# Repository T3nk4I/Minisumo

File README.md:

# Minisumo
Code and Files for all the minisumo and sumo related projects I make, this repository includes codes, schematics, drawings, 3D files and more to make your own minisumo robot.\
**Important: These are mostly personal projects, there might be some errors that will be fixed and updated, but I'm not responsable for any damage or malfunction that is caused by using the codes, files, etc. provided in this repository. If you find any errors in my code, PCBs, or any improvements in the 3D designs feel free to comment so I can correct the design, you can also make a pull request**

*The projects marked in italic are projects that are still on progress*

# Why open source?
When I started there was little to no info on how to make this kind of competition robots, so I want to make newcomers an easy and accesible database.
Also anyone interested in making changes or upgrades can do them depending on their design choice and taste.

# Folders

## PCB's
- Main boards:
  - Tei: PCB for minisumo using arduino nano and TB6612FNG
  - Tenn: PCB for minisumo using arduino nano and DRV8871 drivers
  - Inn BEC: Battery Eliminator Circuit, (AKA buck converter) using XL1509 IC, supports up to 36V and has 5V output, also has a L7805 footprint in the back so it can be adaptable.
  - Ma: PCB using SMD atmega 328P and MSKSEMI RZ7899-MS drivers
  - *Jyo: PCB for microsumo using Seeeduino Xiao and DRV7781 drivers*
- Sensors:
    - QTMicro: Microsized line sensor suitable for minisumo and microsumo robots
## Code
- Basic: basic minisumo code without line sensors and 2 opponent sensors
- *SumoESP: minisumo code for the Arduino Nano ESP model*
- Tamashi-I7ach1: main code used for minisumo robot I7ach1 which uses a ESP32-C3 as the main board
- Tamashi-T4nook1: main code used for minisumo robot T4nook1 which uses a atmega328p as the main controller
- Tamashi-K1tsun3: main code used for minisumo robot K1tsun3 which uses a atmega328p as the main controller
## 3D Data
- Flag System: DAMASHI-FLAG-SYSTEM, used for minisumo robots, compatible with the "OH", "JIN" and "MA-JIN" motor brackets.
- Motor brackets:
  - OH: motor bracket compatible for the minisumo robot chasis in this repository, it can hold 050 style motors
  - JIN: motor bracket compatible for the minisumo robot chasis in this repository, it can hold maxon motors
  - MA-JIN: same as JIN motor bracket, but it can host a qtr-micro line sensor in the back.
- Robots
  - Gyu-Ma-Oh: The base and the chasis files for Gyu-Ma-Oh, 4 oponent sensors and 1 line sensor.
  - T4nook1: The base and the chasis files for T4nook1, 4 oponent sensors and 2 line sensors.
  - K1tsun3: The base and the chasis files for K1tsun3, 5 oponent sensors and 2 line sensors.

# Software that I use
For the most part I try to make all the files as modifiable as possible, but in some cases like the PCB's it's not that possible, so here's a list of software that you can use for the different extensions and file types in this repo.

- 3D data: I mainly use FUSION360 and **[FreeCAD](https://www.freecad.org/)** but I upload the files in .IGES and .STL so you can use any 3D CAD software and slicer software out there to modify and/or print the parts.
- PCB's: I upload the gerbers in zip format for easy fabrication, I also upload a separate gerber file and BOM for **[JLPCB](https://jlcpcb.com/)**  fabrication. As for modifying the files I use **[Kicad](https://www.kicad.org/)** which is a free and open source EDA.
- Code: I use Visual Studio Code with the **[PlatformIO](https://platformio.org/)** extension, but the framework I work on is the arduino framework, so you can use the **[ArduinoIDE](https://www.arduino.cc/en/software)** if you want.

---
You can also visit my ORG. page, **[DENJU DIVISION](https://github.com/DENJU-DIVISION)** where we upload the different files individually, we upload mainly the boards that we have already tested and functioned without problems.

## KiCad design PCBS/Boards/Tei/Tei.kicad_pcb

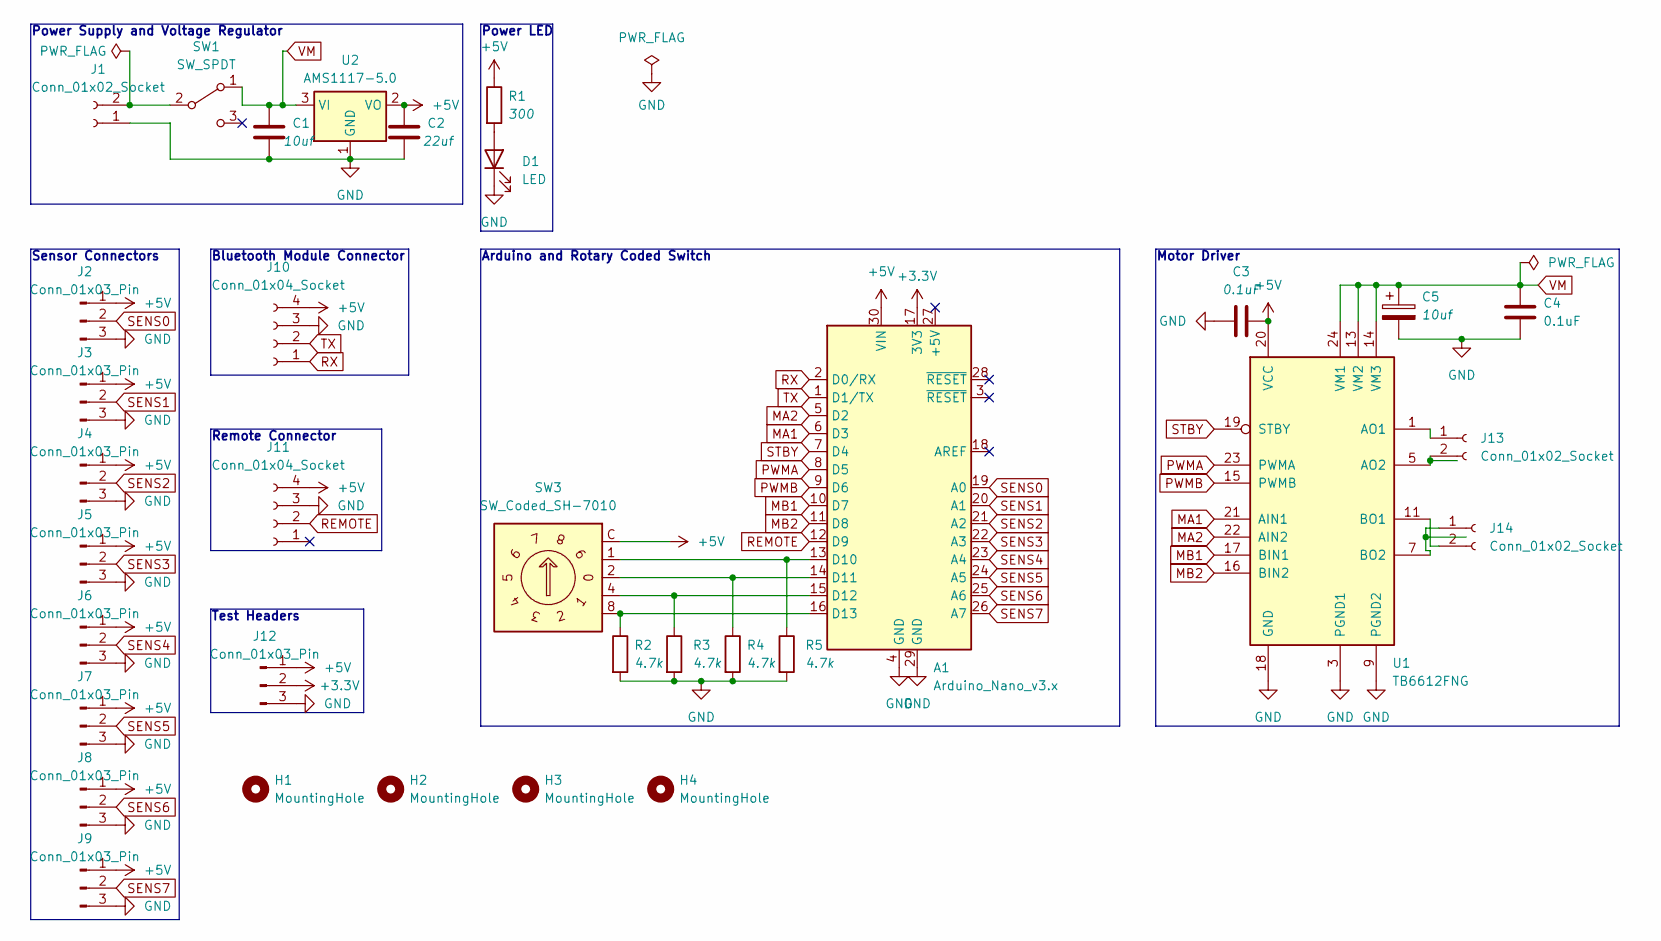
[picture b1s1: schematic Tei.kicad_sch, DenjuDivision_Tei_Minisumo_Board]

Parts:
A1: Arduino_Nano_v3.x; Arduino_Nano
C1: 10uf; C_0805_2012Metric_Pad1.18x1.45mm_HandSolder
C2: 22uf; C_0805_2012Metric_Pad1.18x1.45mm_HandSolder
C3, C4: 0.1uF; C_0805_2012Metric_Pad1.18x1.45mm_HandSolder
C5: 10uf; CP_EIA-3216-18_Kemet-A
D1: LED; LED_0805_2012Metric_Pad1.15x1.40mm_HandSolder
H1, H2, H3, H4: MountingHole; MountingHole_2.2mm_M2
J1: Conn_01x02_Socket; AMASS_XT30U-F_1x02_P5.0mm_Vertical
J2, J3, J4, J5, J6, J7, J8, J9, J12: Conn_01x03_Pin; PinHeader_1x03_P2.54mm_Vertical
J10, J11: Conn_01x04_Socket; PinSocket_1x04_P2.54mm_Vertical
J13, J14: Conn_01x02_Socket; JST_XH_B2B-XH-A_1x02_P2.50mm_Vertical
R1: 300; R_0805_2012Metric_Pad1.20x1.40mm_HandSolder
R2, R3, R4, R5: 4.7k; R_0805_2012Metric_Pad1.20x1.40mm_HandSolder
SW1: SW_SPDT; SW_SPDT_PCM12
SW3: SW_Coded_SH-7010; Nidec_Copal_SH-7010A
U1: TB6612FNG; SSOP-24_5.3x8.2mm_P0.65mm
U2: AMS1117-5.0; SOT-223-3_TabPin2

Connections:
+3.3V: A1.17 (3V3), J12.2
+5V: A1.30 (VIN), C2.1, C3.2, J2.1, J3.1, J4.1, J5.1, J6.1, J7.1, J8.1, J9.1, J10.4, J11.4, J12.1, R1.1, SW3.C, U1.20 (VCC), U2.2 (VO); also elsewhere on the board
GND: A1.4 (GND), A1.29 (GND), C1.2, C2.2, C3.1, C4.1, C5.2, D1.1 (K), J1.1, J2.3, J3.3, J4.3, J5.3, J6.3, J7.3, J8.3, J9.3, J10.3, J11.3, J12.3, R2.2, R3.2, R4.2, R5.2, U1.3 (PGND1), U1.4 (PGND1), U1.9 (PGND2), U1.10 (PGND2), U1.18 (GND), U2.1 (GND); also elsewhere on the board
MA1: A1.6 (D3), U1.21 (AIN1)
MA2: A1.5 (D2), U1.22 (AIN2)
MB1: A1.10 (D7), U1.17 (BIN1)
MB2: A1.11 (D8), U1.16 (BIN2)
unnamed 7: A1.13 (D10), R5.1, SW3.1; also elsewhere on the board
unnamed 8: A1.14 (D11), R4.1, SW3.2; also elsewhere on the board
unnamed 9: A1.15 (D12), R3.1, SW3.4; also elsewhere on the board
unnamed 10: A1.16 (D13), R2.1, SW3.8; also elsewhere on the board
unnamed: D1.2 (A), R1.2
unnamed: J1.2, SW1.2 (B)
unnamed: J13.1, U1.1 (AO1), U1.2 (AO1)
unnamed: J13.2, U1.5 (AO2), U1.6 (AO2)
unnamed: J14.1, U1.7 (BO2), U1.8 (BO2)
unnamed: J14.2, U1.11 (BO1), U1.12 (BO1)
PWMA: A1.8 (D5), U1.23 (PWMA)
PWMB: A1.9 (D6), U1.15 (PWMB)
REMOTE: A1.12 (D9), J11.2; also elsewhere on the board
RX: A1.2 (D0/RX), J10.1; also elsewhere on the board
SENS0: A1.19 (A0), J2.2
SENS1: A1.20 (A1), J3.2
SENS2: A1.21 (A2), J4.2
SENS3: A1.22 (A3), J5.2
SENS4: A1.23 (A4), J6.2
SENS5: A1.24 (A5), J7.2
SENS6: A1.25 (A6), J8.2
SENS7: A1.26 (A7), J9.2
STBY: A1.7 (D4), U1.19 (STBY)
TX: A1.1 (D1/TX), J10.2; also elsewhere on the board
VM: C1.1, C4.2, C5.1, SW1.1 (A), U1.13 (VM2), U1.14 (VM3), U1.24 (VM1), U2.3 (VI)

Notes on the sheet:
Remote Connector
Arduino and Rotary Coded Switch
Sensor Connectors
Test Headers
Bluetooth Module Connector
Power Supply and Voltage Regulator
Power LED
Motor Driver

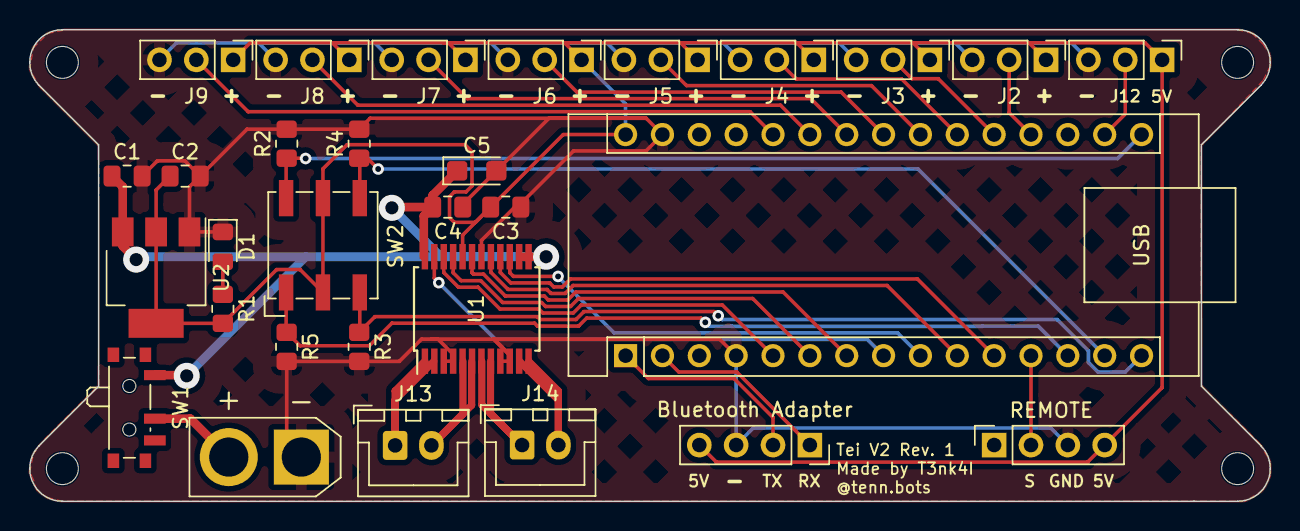
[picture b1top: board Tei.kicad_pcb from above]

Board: 2 copper layers, 85.5 x 32.5 mm, 34 parts (0 on the bottom side), 32 nets.

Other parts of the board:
Bluetooth Adapter: Conn_01x04_Socket; PinSocket_1x04_P2.54mm_Vertical
REMOTE: Conn_01x04_Socket; PinSocket_1x04_P2.54mm_Vertical
SW2: SW_Coded_SH-7010; Nidec_Copal_SH-7010A

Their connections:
+5V: Bluetooth Adapter.4, REMOTE.4, SW2.C; also elsewhere on the board
GND: Bluetooth Adapter.3, REMOTE.3; also elsewhere on the board
unnamed 7: SW2.1; also elsewhere on the board
unnamed 8: SW2.2; also elsewhere on the board
unnamed 9: SW2.4; also elsewhere on the board
unnamed 10: SW2.8; also elsewhere on the board
REMOTE: REMOTE.2; also elsewhere on the board
RX: Bluetooth Adapter.1; also elsewhere on the board
TX: Bluetooth Adapter.2; also elsewhere on the board

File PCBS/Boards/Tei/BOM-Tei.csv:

Comment,Designator,Footprint,LCSC
300,R1,R_0805_2012Metric_Pad1.20x1.40mm_HandSolder,C17661
LED,D1,LED_0805_2012Metric_Pad1.15x1.40mm_HandSolder,C2293
4.7k,"R2,R3,R4,R5",R_0805_2012Metric_Pad1.20x1.40mm_HandSolder,C26022
AMS1117-5.0,U2,SOT-223-3_TabPin2,C351450
0.1uF,"C3,C4",C_0805_2012Metric_Pad1.18x1.45mm_HandSolder,C62768
10uf,C5,CP_EIA-3216-18_Kemet-A,C7177
10uf,C1,C_0805_2012Metric_Pad1.18x1.45mm_HandSolder,C84416
22uf,C2,C_0805_2012Metric_Pad1.18x1.45mm_HandSolder,C86816
TB6612FNG,U1,SSOP-24_5.3x8.2mm_P0.65mm,C88224
Conn_01x03_Pin,J7,PinHeader_1x03_P2.54mm_Vertical,
Conn_01x03_Pin,J6,PinHeader_1x03_P2.54mm_Vertical,
Conn_01x03_Pin,J5,PinHeader_1x03_P2.54mm_Vertical,
Conn_01x03_Pin,J4,PinHeader_1x03_P2.54mm_Vertical,
Arduino_Nano_v3.x,A1,Arduino_Nano,
Conn_01x03_Pin,J2,PinHeader_1x03_P2.54mm_Vertical,
SW_SPDT,SW1,SW_SPDT_PCM12,
Conn_01x03_Pin,J3,PinHeader_1x03_P2.54mm_Vertical,
Conn_01x03_Pin,J8,PinHeader_1x03_P2.54mm_Vertical,
Conn_01x03_Pin,J9,PinHeader_1x03_P2.54mm_Vertical,
Conn_01x02_Socket,J1,AMASS_XT30U-F_1x02_P5.0mm_Vertical,
Conn_01x02_Socket,J14,JST_XH_B2B-XH-A_1x02_P2.50mm_Vertical,
Conn_01x02_Socket,J13,JST_XH_B2B-XH-A_1x02_P2.50mm_Vertical,
MountingHole,H4,MountingHole_2.2mm_M2,
Conn_01x03_Pin,J12,PinHeader_1x03_P2.54mm_Vertical,
MountingHole,H3,MountingHole_2.2mm_M2,
MountingHole,H1,MountingHole_2.2mm_M2,
MountingHole,H2,MountingHole_2.2mm_M2,
SW_Coded_SH-7010,SW2,Nidec_Copal_SH-7010A,

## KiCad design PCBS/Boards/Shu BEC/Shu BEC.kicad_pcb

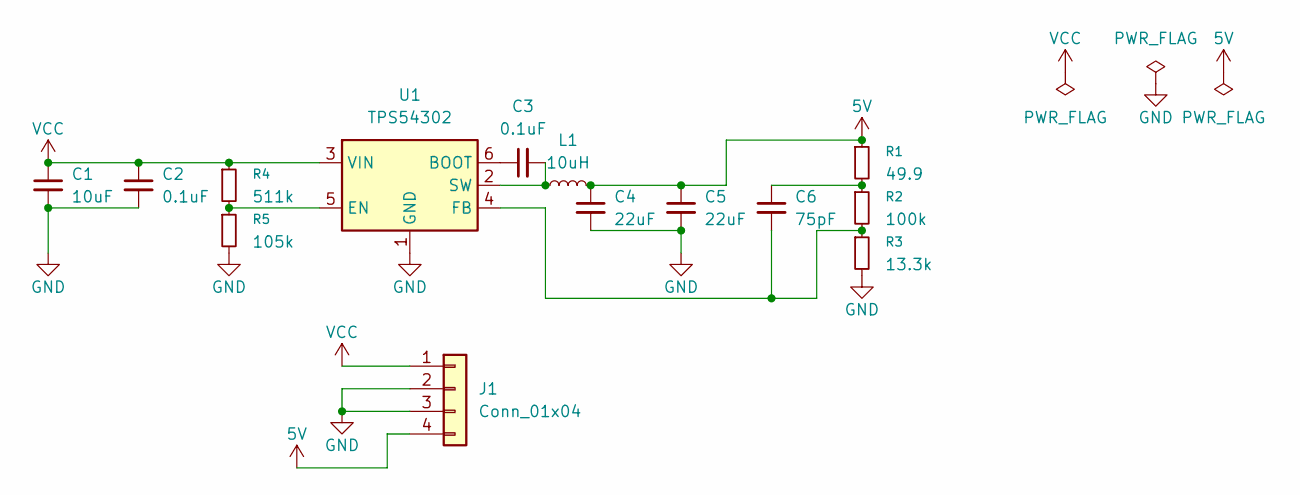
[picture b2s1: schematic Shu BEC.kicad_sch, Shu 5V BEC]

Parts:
C1: 10uF; C_0603_1608Metric
C2, C3: 0.1uF; C_0201_0603Metric
C4, C5: 22uF; C_1206_3216Metric
C6: 75pF; C_0201_0603Metric
J1: Conn_01x04; PinSocket_1x04_P2.54mm_Vertical
L1: 10uH; L_Sunlord_MWSA0518S
R1: 49.9; R_0201_0603Metric
R2: 100k; R_0201_0603Metric
R3: 13.3k; R_0201_0603Metric
R4: 511k; R_0201_0603Metric
R5: 105k; R_0201_0603Metric
U1: TPS54302; SOT-23-6

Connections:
5V: C4.1, C5.1, J1.4, L1.2, R1.1
GND: C1.2, C2.2, C4.2, C5.2, J1.2, J1.3, R3.2, R5.2, U1.1 (GND)
unnamed: C6.1, R1.2, R2.1
unnamed: C3.1, U1.6 (BOOT)
unnamed: R4.2, R5.1, U1.5 (EN)
unnamed: C6.2, R2.2, R3.1, U1.4 (FB)
unnamed: C3.2, L1.1, U1.2 (SW)
VCC: C1.1, C2.1, J1.1, R4.1, U1.3 (VIN)

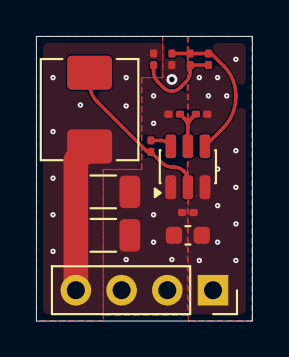
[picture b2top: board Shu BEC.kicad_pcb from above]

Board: 2 copper layers, 12.0 x 15.8 mm, 14 parts (0 on the bottom side), 8 nets.

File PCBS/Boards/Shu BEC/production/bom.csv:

Designator,Footprint,Quantity,Value,LCSC Part #
C1,0603,1,10uF,
"C2, C3",0201,2,0.1uF,
"C4, C5",1206,2,22uF,
C6,0201,1,75pF,
J1,PinSocket_1x04_P2.54mm_Vertical,1,Conn_01x04,
L1,L_Sunlord_MWSA0518S,1,10uH,
R1,0201,1,49.9,
R2,0201,1,100k,
R3,0201,1,13.3k,
R4,0201,1,511k,
R5,0201,1,105k,
U1,SOT-23-6,1,TPS54302,

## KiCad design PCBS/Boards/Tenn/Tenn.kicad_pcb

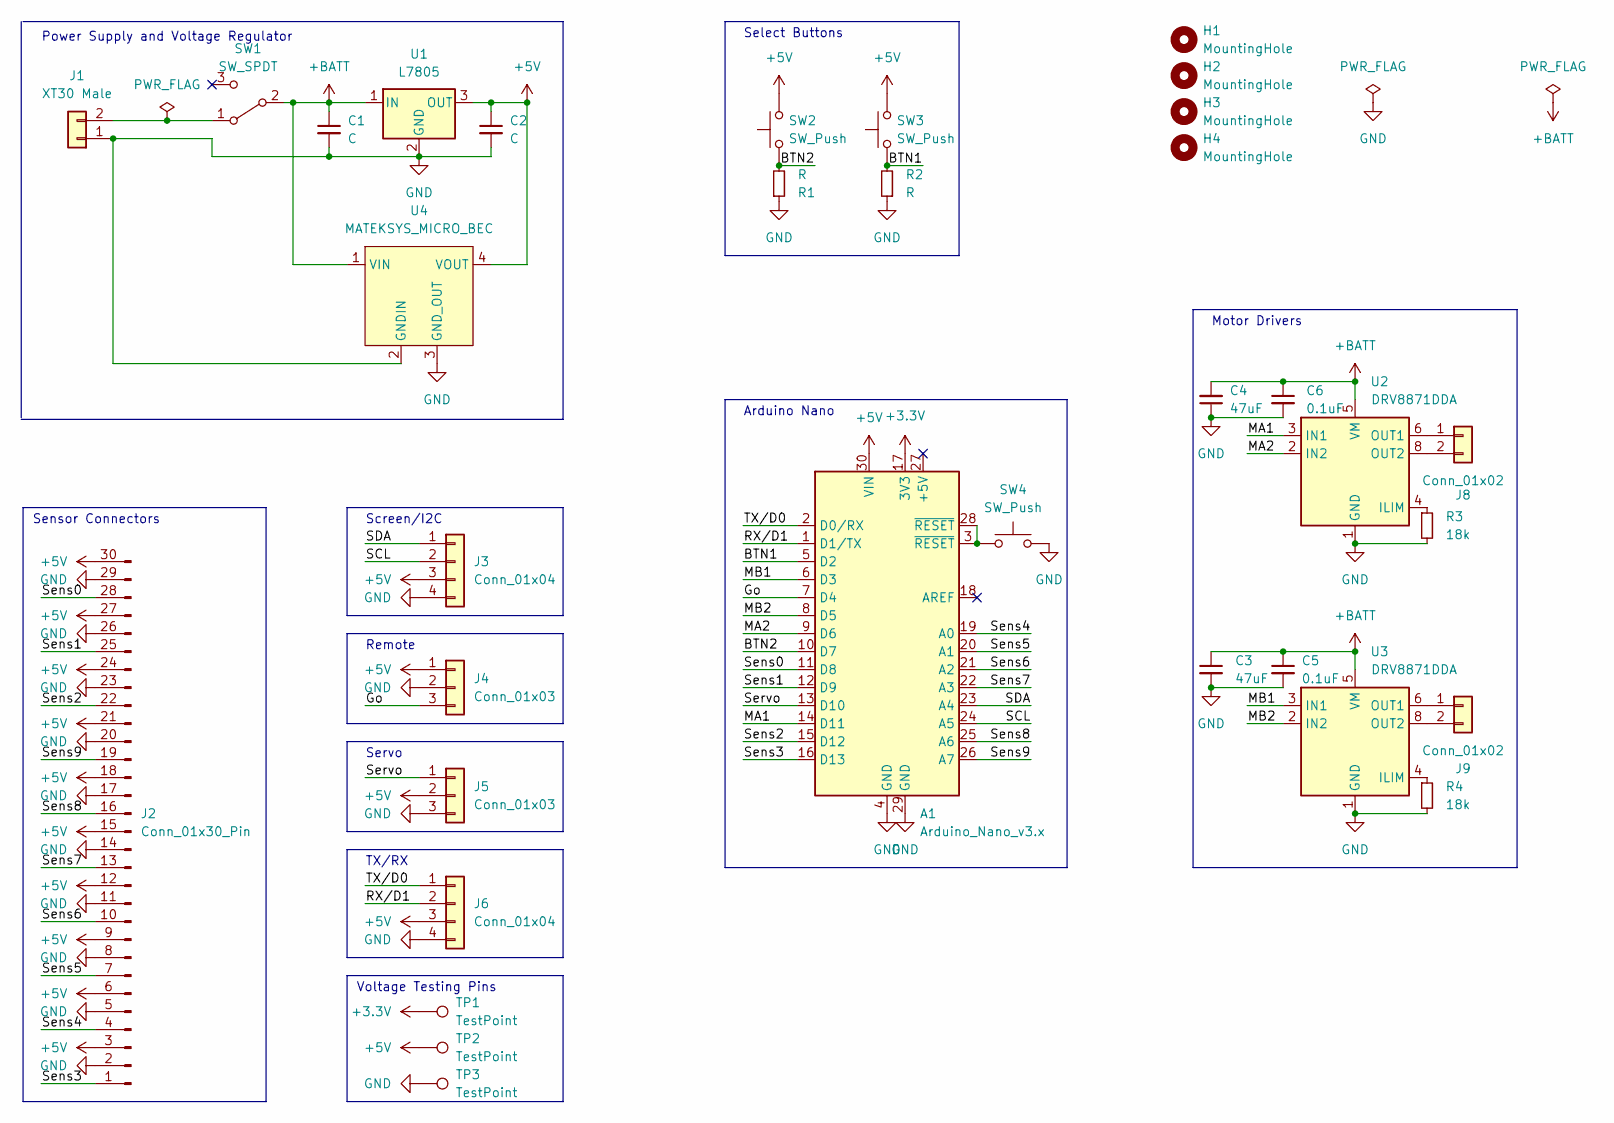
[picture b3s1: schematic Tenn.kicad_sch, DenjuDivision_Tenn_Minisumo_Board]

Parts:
A1: Arduino_Nano_v3.x; Arduino_Nano
C1, C2: C; C_0805_2012Metric_Pad1.18x1.45mm_HandSolder
C3, C4: 47uF; C_1206_3216Metric_Pad1.33x1.80mm_HandSolder
C5, C6: 0.1uF; C_0805_2012Metric_Pad1.18x1.45mm_HandSolder
H1, H2, H3, H4: MountingHole; MountingHole_2.2mm_M2_ISO7380
J1: XT30 Male; AMASS_XT30U-M_1x02_P5.0mm_Vertical
J2: Conn_01x30_Pin; PinSocket_1x30_P2.54mm_Vertical
J3, J6: Conn_01x04; PinSocket_1x04_P2.54mm_Vertical
J4: Conn_01x03; PinSocket_1x03_P2.54mm_Vertical
J5: Conn_01x03; PinHeader_1x03_P2.54mm_Vertical
J8, J9: Conn_01x02; JST_XH_B2B-XH-A_1x02_P2.50mm_Vertical
R1, R2: R; R_0805_2012Metric_Pad1.20x1.40mm_HandSolder
R3, R4: 18k; R_0805_2012Metric_Pad1.20x1.40mm_HandSolder
SW1: SW_SPDT; SW_Slide_SPDT_Straight_CK_OS102011MS2Q
SW2, SW3: SW_Push; SW_Push_1P1T_NO_Vertical_Wuerth_434133025816
SW4: SW_Push; SW_SPST_B3U-1000P
TP1, TP2, TP3: TestPoint; TestPoint-0.75mm
U1: L7805; TO-252-2
U2, U3: DRV8871DDA; Texas_HTSOP-8-1EP_3.9x4.9mm_P1.27mm_EP2.95x4.9mm_Mask2.4x3.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
U4: MATEKSYS_MICRO_BEC; MATEKSYS MICRO BEC

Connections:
+3.3V: A1.17 (3V3), TP1.1 (1_1)
+5V: A1.30 (VIN), C2.1, J2.3, J2.6, J2.9, J2.12, J2.15, J2.18, J2.21, J2.24, J2.27, J2.30, J3.3, J4.1, J5.2, J6.3, SW2.2, SW3.2, TP2.1 (1_1), U1.3 (OUT), U4.4 (VOUT)
+BATT: C1.1, C3.1, C4.2, C5.1, C6.1, SW1.2 (B), U1.1 (IN), U2.5 (VM), U3.5 (VM), U4.1 (VIN)
/BTN1: A1.5 (D2), R2.2, SW3.1
/BTN2: A1.10 (D7), R1.2, SW2.1
/Go: A1.7 (D4), J4.3
/MA1: A1.14 (D11), U2.3 (IN1)
/MA2: A1.9 (D6), U2.2 (IN2)
/MB1: A1.6 (D3), U3.3 (IN1)
/MB2: A1.8 (D5), U3.2 (IN2)
/RX/D1: A1.1 (D1/TX), J6.2
/SCL: A1.24 (A5), J3.2
/SDA: A1.23 (A4), J3.1
/Sens0: A1.11 (D8), J2.28
/Sens1: A1.12 (D9), J2.25
/Sens2: A1.15 (D12), J2.22
/Sens3: A1.16 (D13), J2.1
/Sens4: A1.19 (A0), J2.4
/Sens5: A1.20 (A1), J2.7
/Sens6: A1.21 (A2), J2.10
/Sens7: A1.22 (A3), J2.13
/Sens8: A1.25 (A6), J2.16
/Sens9: A1.26 (A7), J2.19
/Servo: A1.13 (D10), J5.1
/TX/D0: A1.2 (D0/RX), J6.1
GND: A1.4 (GND), A1.29 (GND), C1.2, C2.2, C3.2, C4.1, C5.2, C6.2, J1.1, J2.2, J2.5, J2.8, J2.11, J2.14, J2.17, J2.20, J2.23, J2.26, J2.29, J3.4, J4.2, J5.3, J6.4, R1.1, R2.1, R3.2, R4.2, SW4.2, TP3.1 (1_1), U1.2 (GND), U2.1 (GND), U2.7 (GND), U2.9 (GND), U3.1 (GND), U3.7 (GND), U3.9 (GND), U4.2 (GNDIN), U4.3 (GND_OUT)
unnamed: A1.3 (~RESET), A1.28 (~RESET), SW4.1
unnamed: J1.2, SW1.1 (A)
unnamed: J8.1, U2.6 (OUT1)
unnamed: J8.2, U2.8 (OUT2)
unnamed: J9.1, U3.6 (OUT1)
unnamed: J9.2, U3.8 (OUT2)
unnamed: R3.1, U2.4 (ILIM)
unnamed: R4.1, U3.4 (ILIM)

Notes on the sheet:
Arduino Nano
Sensor Connectors
Screen/I2C
Servo
Select Buttons
Motor Drivers
Remote
TX/RX
Power Supply and Voltage Regulator
Voltage Testing Pins

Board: 2 copper layers, 34 parts (3 on the bottom side), 34 nets, no tracks yet.

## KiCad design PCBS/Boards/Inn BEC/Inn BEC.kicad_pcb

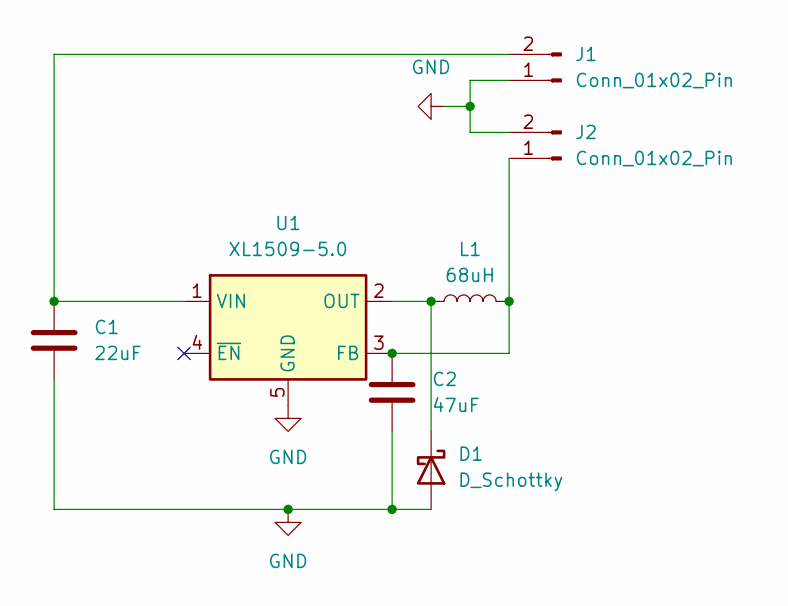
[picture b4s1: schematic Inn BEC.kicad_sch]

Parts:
C1: 22uF; C_0805_2012Metric_Pad1.18x1.45mm_HandSolder
C2: 47uF; C_1210_3225Metric_Pad1.33x2.70mm_HandSolder
D1: D_Schottky; D_SMA
J1, J2: Conn_01x02_Pin; SolderWire-0.1sqmm_1x02_P3.6mm_D0.4mm_OD1mm
L1: 68uH; L_Bourns-SRN4018
U1: XL1509-5.0; SOIC-8_3.9x4.9mm_P1.27mm

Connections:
GND: C1.2, C2.2, D1.2 (A), J1.1, J2.2, U1.5 (GND), U1.6 (GND), U1.7 (GND), U1.8 (GND)
unnamed: D1.1 (K), L1.1, U1.2 (OUT)
unnamed: C1.1, J1.2, U1.1 (VIN)
unnamed: C2.1, J2.1, L1.2, U1.3 (FB)

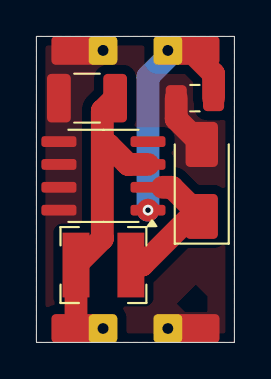
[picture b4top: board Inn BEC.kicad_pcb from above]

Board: 2 copper layers, 11.0 x 17.0 mm, 7 parts (0 on the bottom side), 4 nets.

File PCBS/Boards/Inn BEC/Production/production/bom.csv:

Designator,Footprint,Quantity,Value,LCSC Part #
"C1_40, C1_39, C1_38, C1_37, C1_36, C1_35, C1_34, C1_33, C1_32, C1_31, C1_30, C1_29, C1_28, C1_27, C1_26, C1_25, C1_24, C1_23, C1_22, C1_21, C1_20, C1_19, C1_18, C1_17, C1_16, C1_15, C1_14, C1_13, C1_12, C1_11, C1_10, C1_9, C1_8, C1_7, C1_6, C1_5, C1_4, C1_3, C1_2, C1",0805,40,22uF,
"C2_40, C2_39, C2_38, C2_37, C2_36, C2_35, C2_34, C2_33, C2_32, C2_31, C2_30, C2_29, C2_28, C2_27, C2_26, C2_25, C2_24, C2_23, C2_22, C2_21, C2_20, C2_19, C2_18, C2_17, C2_16, C2_15, C2_14, C2_13, C2_12, C2_11, C2_10, C2_9, C2_8, C2_7, C2_6, C2_5, C2_4, C2_3, C2_2, C2",1210,40,47uF,
"D1_40, D1_39, D1_38, D1_37, D1_36, D1_35, D1_34, D1_33, D1_32, D1_31, D1_30, D1_29, D1_28, D1_27, D1_26, D1_25, D1_24, D1_23, D1_22, D1_21, D1_20, D1_19, D1_18, D1_17, D1_16, D1_15, D1_14, D1_13, D1_12, D1_11, D1_10, D1_9, D1_8, D1_7, D1_6, D1_5, D1_4, D1_3, D1_2, D1",D_SMA,40,D_Schottky,
"J1_40, J1_39, J1_38, J1_37, J1_36, J1_35, J1_34, J1_33, J1_32, J1_31, J1_30, J1_29, J1_28, J1_27, J1_26, J1_25, J1_24, J1_23, J1_22, J1_21, J1_20, J1_19, J1_18, J1_17, J1_16, J1_15, J1_14, J1_13, J1_12, J1_11, J1_10, J1_9, J1_8, J1_7, J1_6, J1_5, J1_4, J1_3, J1_2, J1, J2_40, J2_39, J2_38, J2_37, J2_36, J2_35, J2_34, J2_33, J2_32, J2_31, J2_30, J2_29, J2_28, J2_27, J2_26, J2_25, J2_24, J2_23, J2_22, J2_21, J2_20, J2_19, J2_18, J2_17, J2_16, J2_15, J2_14, J2_13, J2_12, J2_11, J2_10, J2_9, J2_8, J2_7, J2_6, J2_5, J2_4, J2_3, J2_2, J2",SolderWire-0.1sqmm_1x02_P3.6mm_D0.4mm_OD1mm,80,Conn_01x02_Pin,
"L1_40, L1_39, L1_38, L1_37, L1_36, L1_35, L1_34, L1_33, L1_32, L1_31, L1_30, L1_29, L1_28, L1_27, L1_26, L1_25, L1_24, L1_23, L1_22, L1_21, L1_20, L1_19, L1_18, L1_17, L1_16, L1_15, L1_14, L1_13, L1_12, L1_11, L1_10, L1_9, L1_8, L1_7, L1_6, L1_5, L1_4, L1_3, L1_2, L1",L_Bourns-SRN4018,40,68uH,
"U1_40, U1_39, U1_38, U1_37, U1_36, U1_35, U1_34, U1_33, U1_32, U1_31, U1_30, U1_29, U1_28, U1_27, U1_26, U1_25, U1_24, U1_23, U1_22, U1_21, U1_20, U1_19, U1_18, U1_17, U1_16, U1_15, U1_14, U1_13, U1_12, U1_11, U1_10, U1_9, U1_8, U1_7, U1_6, U1_5, U1_4, U1_3, U1_2, U1",SOIC-8_3.9x4.9mm_P1.27mm,40,XL1509-5.0,

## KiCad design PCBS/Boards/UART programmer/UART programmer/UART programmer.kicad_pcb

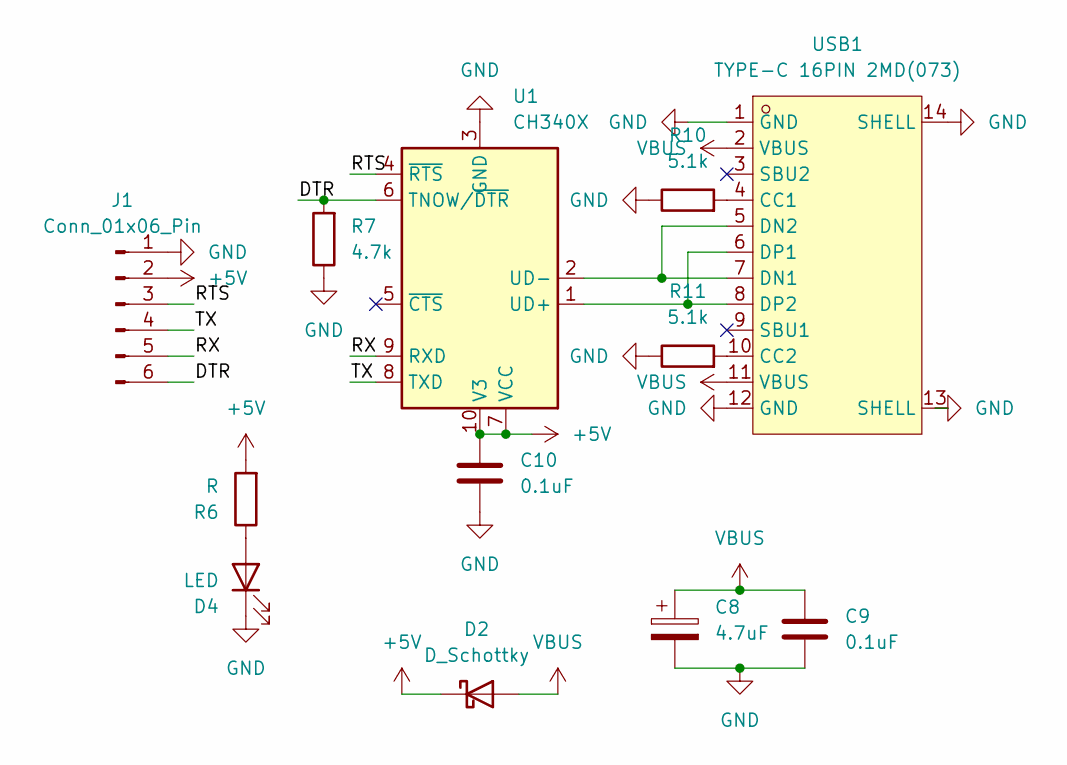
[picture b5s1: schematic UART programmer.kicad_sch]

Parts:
C8: 4.7uF; C_0805_2012Metric
C9, C10: 0.1uF; C_0805_2012Metric
D2: D_Schottky; D_0805_2012Metric
D4: LED; LED_0603_1608Metric
J1: Conn_01x06_Pin; JST_XH_S6B-XH-A-1_1x06_P2.50mm_Horizontal
R6: R; R_0603_1608Metric
R7: 4.7k; R_0603_1608Metric
R10, R11: 5.1k; R_0603_1608Metric
U1: CH340X; MSOP-10_3x3mm_P0.5mm
USB1: TYPE-C 16PIN 2MD(073); USB-C-SMD_TYPE-C-6PIN-2MD-073; LCSC Part C2765186

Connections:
+5V: C10.2, D2.1 (K), J1.2, R6.2, U1.7 (VCC), U1.10 (V3)
/DTR: J1.6, R7.2, U1.6 (TNOW/~DTR)
/RTS: J1.3, U1.4 (~RTS)
/RX: J1.5, U1.9 (RXD)
/TX: J1.4, U1.8 (TXD)
GND: C8.2, C9.1, C10.1, D4.1 (K), J1.1, R7.1, R10.1, R11.1, U1.3 (GND), USB1.1 (GND), USB1.12 (GND), USB1.13 (SHELL), USB1.14 (SHELL)
unnamed: D4.2 (A), R6.1
unnamed: U1.1 (UD+), USB1.6 (DP1), USB1.8 (DP2)
unnamed: U1.2 (UD-), USB1.5 (DN2), USB1.7 (DN1)
unnamed: R10.2, USB1.4 (CC1)
unnamed: R11.2, USB1.10 (CC2)
VBUS: C8.1, C9.2, D2.2 (A), USB1.2 (VBUS), USB1.11 (VBUS)

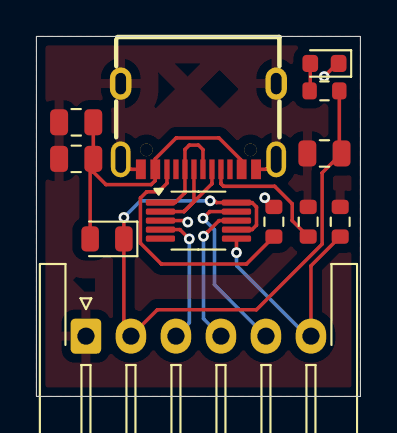
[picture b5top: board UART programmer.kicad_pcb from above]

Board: 2 copper layers, 18.0 x 20.0 mm, 12 parts (0 on the bottom side), 12 nets.

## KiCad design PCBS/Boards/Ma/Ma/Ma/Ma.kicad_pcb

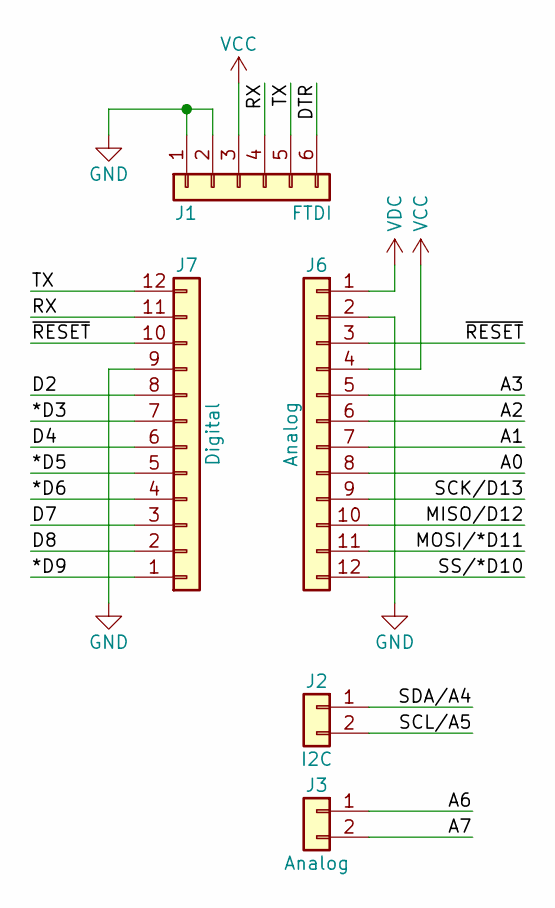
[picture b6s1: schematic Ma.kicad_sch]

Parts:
J1: FTDI; PinHeader_1x06_P2.54mm_Horizontal
J2: I2C; PinHeader_1x02_P2.54mm_Vertical
J3: Analog; PinHeader_1x02_P2.54mm_Vertical
J6: Analog; PinHeader_1x12_P2.54mm_Vertical
J7: Digital; PinHeader_1x12_P2.54mm_Vertical

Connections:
/*D3: J7.7
/*D5: J7.5
/*D6: J7.4
/*D9: J7.1
/A0: J6.8
/A1: J6.7
/A2: J6.6
/A3: J6.5
/A6: J3.1
/A7: J3.2
/D2: J7.8
/D4: J7.6
/D7: J7.3
/D8: J7.2
/DTR: J1.6
/MISO/D12: J6.10
/MOSI/*D11: J6.11
/RX: J1.4, J7.11
/SCK/D13: J6.9
/SCL/A5: J2.2
/SDA/A4: J2.1
/SS/*D10: J6.12
/TX: J1.5, J7.12
/~RESET: J6.3, J7.10
GND: J1.1, J1.2, J6.2, J7.9
VCC: J1.3, J6.4
VDC: J6.1

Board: 2 copper layers, 5 parts (2 on the bottom side), 5 nets, no tracks yet.

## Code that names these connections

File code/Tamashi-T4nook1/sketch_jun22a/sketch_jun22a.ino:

#include <Arduino.h>
#include <Servo.h>
#include <Wire.h>
#include <Adafruit_GFX.h>
#include <Adafruit_SSD1306.h>

#define SCREEN_WIDTH 128 //defines the width of the OLED screen
#define SCREEN_HEIGHT 64 //defines the height of the OLED screen
Adafruit_SSD1306 oled(SCREEN_WIDTH, SCREEN_HEIGHT, &Wire, -1); //sets up the OLED screen with the defined width and height

// defines sensor input pins
#define SENS0 8 // line sensor LEFT
#define SENS1 9  //left diagonal sensor
#define SENS2 12  //front left sensor
#define SENS3 13  //line sensor RIGHT 
#define SENS4 A0  //right diagonal sensor
#define SENS5 A1  //front right sensor
#define SENS6 A2  
#define SENS7 A3  
#define SENS8 A6 // only analog inputs
#define SENS9 A7 // only analog inputs

// defines motor and servo output pins
#define MA1 11
#define MA2 6
#define MB2 3
#define MB1 5
#define SERVO 10
Servo FLAG;

// defines remote and button input pin
#define REMOTE 4
#define BTN2 2
#define BTN1 7

byte rut = 1;
bool test_mode;
int ang;

void setup() {
  if(!oled.begin(SSD1306_SWITCHCAPVCC, 0x3c)){
    Serial.println(F("SSD1306 allocation failed"));
    while (true);
  }
  delay(2000);
  oled.clearDisplay();
  oled.setCursor(0, 0);
  FLAG.attach(SERVO);
  pinMode(SENS0, INPUT);
  pinMode(SENS1, INPUT);
  pinMode(SENS2, INPUT);
  pinMode(SENS3, INPUT);
  pinMode(SENS4, INPUT);
  pinMode(SENS5, INPUT);
  pinMode(SENS6, INPUT);
  pinMode(SENS7, INPUT);
  pinMode(SENS8, INPUT); 
  pinMode(SENS9, INPUT);

  pinMode(REMOTE, INPUT);
  pinMode(BTN1, INPUT_PULLUP);
  pinMode(BTN2, INPUT_PULLUP);

  pinMode(MA1, OUTPUT);
  pinMode(MA2, OUTPUT);
  pinMode(MB1, OUTPUT);
  pinMode(MB2, OUTPUT);
  FLAG.write(90);
  Serial.begin(9600);
}

void oledWrite(String current_mode) { //function to show on screen the current mode
  oled.clearDisplay();
  oled.setTextSize(3);
  oled.setCursor(0, 20);
  oled.setTextColor(WHITE);
  oled.println(current_mode);
  oled.display();
  Serial.println(current_mode);
}

void stop(int t){
  analogWrite(MA1,255);
  analogWrite(MA2,255);
  analogWrite(MB1,255);
  analogWrite(MB2,255);
  delay(t);
}

void off(){
  analogWrite(MA1,0);
  analogWrite(MA2,0);
  analogWrite(MB1,0);
  analogWrite(MB2,0);
}

void forwards(int a, int b, int t){
  analogWrite(MA1, a);
  digitalWrite(MA2, LOW);
  analogWrite(MB1, b);
  digitalWrite(MB2, LOW);
  delay(t);
}

void backwards(int a, int b, int t){
  digitalWrite(MA1, LOW);
  analogWrite(MA2, a);
  digitalWrite(MB1, LOW);
  analogWrite(MB2, b);
  delay(t);
}

void left(int a, int b, int t){
  analogWrite(MA1,a);
  digitalWrite(MA2, LOW);
  digitalWrite(MB1, LOW);
  analogWrite(MB2, b);
  delay(t);
}

void right(int a, int b, int t){
  digitalWrite(MA1, LOW);
  analogWrite(MA2, a);
  analogWrite(MB1, b);
  digitalWrite(MB2, LOW);
  delay(t);
}

byte sensval(){
  bool FRONT_R = !digitalRead(SENS3);
  byte FRONT_L = !digitalRead(SENS0) * 2;
  byte RIGHT = digitalRead(SENS5) * 4;
  byte LEFT = digitalRead(SENS2) *8;
  byte total = FRONT_R + FRONT_L + RIGHT + LEFT;
  return total;
}

byte lineval(){
  bool LINE_R = digitalRead(SENS4);
  byte LINE_L = digitalRead(SENS1) * 2;
  byte total = LINE_R + LINE_L;
  return total;
}

void MainBattle() {
  while (digitalRead(REMOTE) == HIGH){
    FLAG.write(ang);
    switch (lineval()){
    case 0:
      backwards(175,175,100);
      right(255, 255, 175);
      break;
    
    case 1:
      backwards(175,175,70);
      right(255, 255, 100);
      break;

    case 2:
      backwards(175,175,70);
      left(255, 255, 100);
      break;

    case 3:
      switch (sensval()){
        case 1:
          forwards(75,100,20);
          break;

        case 2:
          forwards(100,75,20);
          break;

        case 3:
          forwards(255,255,30);
          break;

        case 4:
          right(255,255,20);
          break;

        case 5:
          right(255,255,15);
          break;

        case 7:
          right(255,255,50);
          break;
          
        case 8:
          left(255,255,20);
          break;

        case 10:
          left(255,255,15);
          break;

        case 11:
          left(255,255,50);
          break;

        case 15:
          forwards(175,175,30);
          break;

        default:
          switch (rut){
          case 7:
            right(50,50,20); 
            break;
          
          default:
            forwards(40,25,80);
            delay(200);
            break;
          }
      }
      break;
    }
  }
  if (digitalRead(REMOTE)==LOW){
    off();
  }
}

void rocket(){
  while (digitalRead(REMOTE)==HIGH){
    forwards(225,255,200);
    ang = 180;
    MainBattle();
  }
  off();
}

void curveL(){
  while (digitalRead(REMOTE)==HIGH){
    forwards(225,25,400);
    ang = 180;
    MainBattle();
  }
  off();
}

void curveR(){
  while (digitalRead(REMOTE)==HIGH){
    forwards(25,225,400);
    ang = 0;
    MainBattle();
  }
  off();
}

void edgingL(){
  while (digitalRead(REMOTE)==HIGH){
    forwards(175,175,275);
    right(255,255,150);
    ang = 180;  //left
    MainBattle();
  }
  off();
}

void edgingR(){
  while (digitalRead(REMOTE)==HIGH){
    forwards(175,175,275);
    left(255,255,150);
    ang = 0;  //right
    MainBattle();
  }
  off();
}

void motortest(){
  while (digitalRead(REMOTE)==HIGH){
    for(int i = 0; i<=255; i++){
      forwards(i,i,10);
    }
    for(int i = 0; i<=255; i++){
      backwards(i,i,10);
    }
    for(int i = 0; i<=255; i++){
      right(i,i,10);
    }
    for(int i = 0; i<=255; i++){
      left(i,i,10);
    }
  }
  
}

void sensor_test(){
  while (digitalRead(REMOTE)==HIGH){
    if(digitalRead(BTN1)==HIGH){
      test_mode = true;
    }
    if(digitalRead(BTN2)==HIGH){
      test_mode = false;
    }
    switch (test_mode){
    case 0:
      oledWrite(String(sensval()));
      break;
    
    case 1:
      oledWrite(String(lineval()));
      break;
    }
  }
}

void loop(){
  off();
  FLAG.write(90);
  if (digitalRead(BTN1)==HIGH){  //increase routine cout if button 1 is pressed
    delay(150); //increase delay for less sensitivity (longer press), decrease for more sensitivity (shorter press)
    rut++;
    Serial.println("Button 1 pressed");
    if(rut>=12){
      rut=1;
    }
  }
  if (digitalRead(BTN2)==HIGH){  //decrease routine cout if button 2 is pressed
    delay(150);
    rut--;
    Serial.println("Button 2 pressed");
    if(rut<=0){
      rut=11;
    }       
  }
  switch (rut){
    case 1: //Routine #1;
      oledWrite("Normal FR");
      ang = 0;
      MainBattle();
      break;

    case 2:
      oledWrite("Normal FL");
      ang = 180;
      MainBattle();
      break;

    case 3:
      oledWrite("Rocket");
      rocket();
      break;
    
    case 4:
      oledWrite("Curve L");
      curveL();
      break;

    case 5:
      oledWrite("Curve R");
      curveR();
      break;

    case 6:
      oledWrite("Edging L");
      edgingL();
      break;

    case 7:
      oledWrite("Edging R");
      edgingR();
      break;

    case 8:
      oledWrite("Mexican");
      MainBattle();
      break;
    
    case 9:
      oledWrite("Motor Test");
      motortest();
      break;
    
    case 10:
      oledWrite("Sensor Test");
      sensor_test();
      break;

    case 11:
      oledWrite("self_destruct");
      break;
  }
}

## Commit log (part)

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2023-09-15 Added Basic
    Added Basic, program for basic minisumo robots, no line sensors, 2 opponent sensors.
2023-09-15 Update and rename Basic.ino to code/Basic.ino
    Created a new folder called code and saved basic in there
2023-09-21 Create Microsumo File
2023-09-22 Uploaded new version of microsumo base
    Corrected an error with the tolerances of the space of the middle sensor
2023-10-25 shmin cloned this repository
2023-10-25 Changed flag angle value to 90 degrees
2024-01-15 Created Description.md
2024-01-15 Added Tei schematic
2024-02-01 Added Gerber and BOM files
    Added gerber and BOM files optimized for production in JLCPCB
2024-02-25 Modified Readme
2024-02-25 added new program for robot I7ach1
2024-02-25 modified tamashi-I7ach1
2024-02-25 deleted Tamashi-I7ach1 due to an error making it a nested git repository
2024-02-25 added tamashi-i7ach1
2024-02-25 changed name of sketch_jun22a to tamashi-t4nook1
2024-02-25 modified tamashi i7ach1
2024-02-26 added new 3D files for 3 different motor brackets
2024-03-14 fixed some errors in main.cpp in I7ach1 code
2024-03-14 Added Sensor test mode
2024-03-14 Added combat mode Rocket
2024-03-14 fixed issue with SensTest
2024-03-14 fixed errors in SensTest
2024-03-15 added line test function
2024-03-15 updated LineTest mode
2024-03-15 made changes in I7ach1 main.cpp
2024-03-16 activated some cases in main_battle in I7ach1 code
2024-03-16 asjusted some values in main battle in Tamashi-I7ach1 main
2024-03-16 fixed some issues in the differents strats in Tamashi-I7ach1
2024-03-31 Added all the KiCad files for Tei Board
2024-03-31 Added extra KiCad files for easier modification of Tei Board
2024-03-31 Created Tenn Board files, added schematic, BOM and more KiCad files
2024-04-06 created gitignore, ignores personal vscode settings
2024-04-13 updated Tei board PCB, all components now in place
2024-04-13 changed Tenn PCB, all components now in place
2024-04-23 Created Tamashi K1tsun3 in /code
2024-04-24 updates tamashi-k1tsun3
2024-04-24 Updates Tamashii-K1tsun3
2024-04-24 updates Tamashii-K1tsun3 main cpp
2024-04-26 Updated tamashii-k1tsun3
2024-04-28 assined correct pins in define section at main cpp in k1tsun3-tamashii
2024-04-28 updates main cpp in K1tsun3-Tamashii
2024-05-03 Updates nets and adds tracks in pcb file
2024-05-03 updates pcb nets and tracks
2024-05-03 updates nets and tracks
2024-05-05 updates tenn PCB board, changes some connections and netclasses
2024-05-06 uploads 3D data of bases and chasis of Gyu-Ma-Oh, T4nook1 and K1tsun3
2024-05-15 updates the files in Tenn PCB board
2024-05-19 updates PCB of tenn board
2024-05-21 updates tenn.pdf in tenn board
2024-05-27 updates tenn board, adds gerber files, ready for production
2024-05-29 updates production files of tenn board
2024-05-29 updates readme
2024-05-30 creates tamashii ari, main code for ari microsumo robot
2024-06-04 updates damashi flag system, adds long stem versions of the gears as well
2024-06-04 adds image for the placement of components in the qt micro sensor
2024-06-13 updates jucad tenn board file, now OLED screen pins are in the correct orientation
2024-06-13 changes revision of tenn board from 2.0 to 2.1
2024-06-21 Updates Tamashii K1tsun3, changes pinouts for Tenn board rev 2 and adds OLED and buttons functionality
2024-06-21 Updates Tamashii K1tsun3, adds more routines
2024-06-22 commented some code in k1tsune tamashii
2024-06-26 created inn BEC board
2024-07-05 Updates footprints in tenn.pcb, changes cap tantulum to 0805
2024-07-09 updates tenn pcb, redesign to rev 2.2, fixed problem with button not working
2024-07-10 Updaes README
2024-07-10 fixes error with tenn.pcb making it not possible to open, restpred files from backup
2024-07-10 Updates Tenn, Rev 2.2 now fixes issues with the buttons not working correctly, the screen orientation, it also uses new components, supporting up to 6s theorical
2024-07-16 added back silkscreen to tenn board
2024-08-05 Updates tenn pcb with new graphics and adds updated gerber and production files
2024-09-06 updates Tamashi ari, working partially
2024-09-19 Create LICENSE
2024-10-27 updatets K1tsun3 Tamashii, implements testmodes for Tenn board, and adds functionality to the buttons
2024-11-02 updates k1tsun3 tamashii and creates new t4nook1 tamashii
2024-11-02 updates files for Tamashii
2024-11-02 updates Tamashii k1tsun3, edging left and right, now working correctly and tested
2024-12-02 Create Tenn_Board_With_Icons.ino
    Add code for displaying strategies with icons on Tenn board for a Minisumo robot
2025-01-24 Cahnges some files in PCB/tenn
2025-01-24 Changes some files that couldn't load in PCB/tenn
2025-04-04 adds more battle modes to k1tsun3 and t4nook1
2025-04-08 changes values for default search mode to go more slowly
2025-05-15 README.md の更新
2025-05-23 adds new attack modes (still subject to tests)
2025-05-25 uploads code for Gyu-Tenn-Oh
2025-05-30 updates code in tamashii-gyu, changes the function sensval to more bare-metal C code
2025-06-08 updates files for INN BEC, adds production files and panelized version
2025-06-08 updates files on tenn pcb, fixes error with GND not being connected
2025-06-08 updates files of tenn pcb, changes foot print of 47uf capacitor, fixes unconnected vias and traces, adds Arduino GPIO references in the backside for easier understanding of the board
2025-07-28 creates schematic and PCB for MA minisumo board
2025-07-28 updates MA PCB, adds logos
2025-07-28 adds schematic PDF, panelized version of the boards and Production files for MA PCB
2025-10-31 updates values for flag position in T4nook1 Tamashii
2025-10-31 adds variables for new and easier integration of modes TEST ONLY, NOT IMPLEMENTED YET
2026-05-15 updated readme and PCB files
